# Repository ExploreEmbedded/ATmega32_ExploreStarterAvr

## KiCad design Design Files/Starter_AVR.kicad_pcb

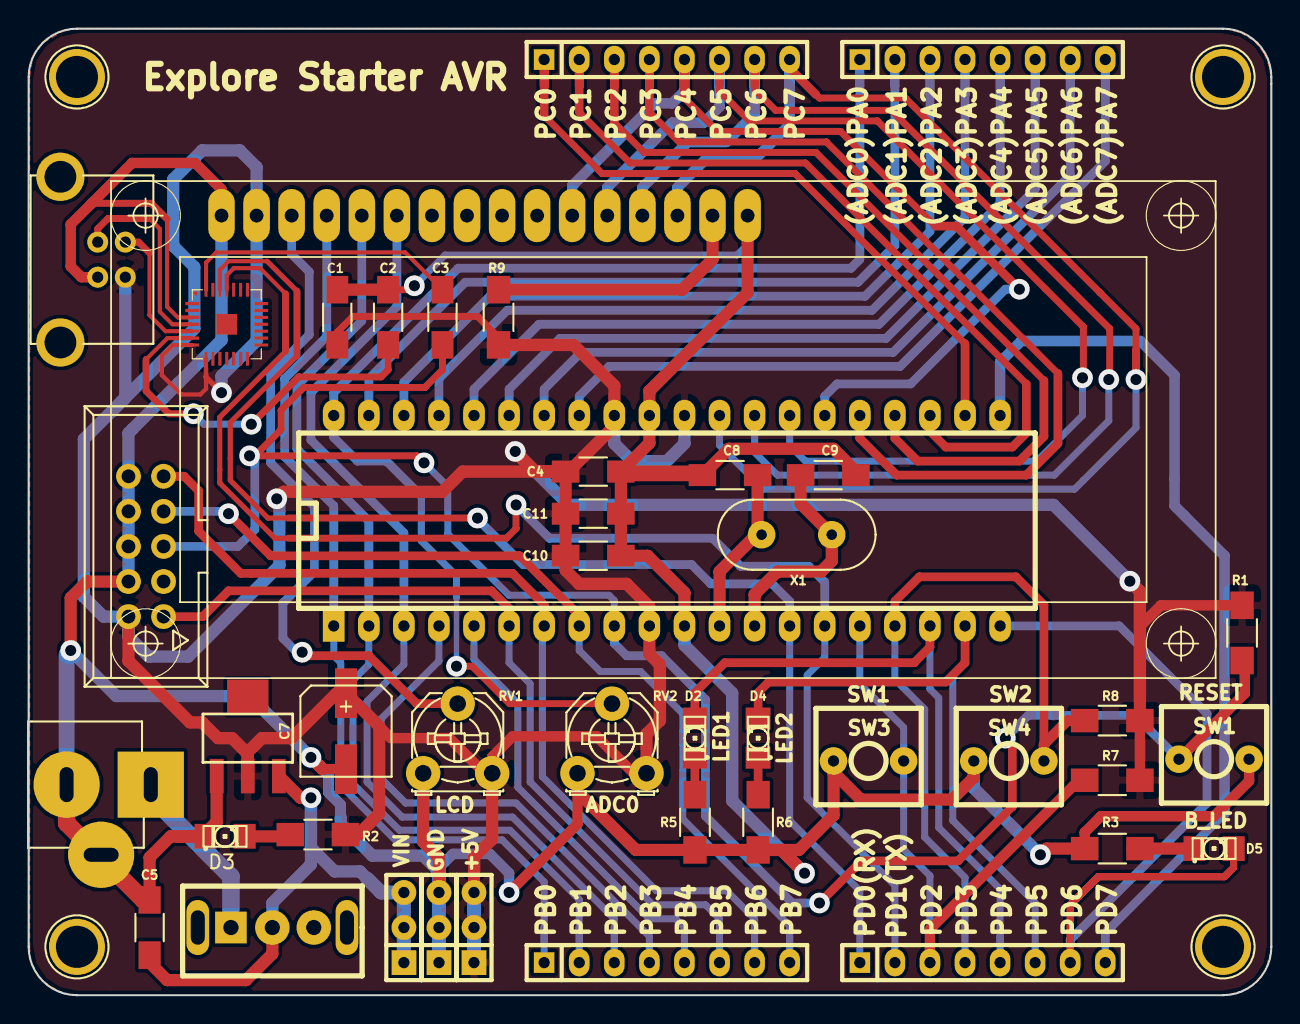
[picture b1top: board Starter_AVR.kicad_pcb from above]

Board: 2 copper layers, 90.0 x 70.0 mm, 47 parts (0 on the bottom side), 49 nets.

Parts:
C1, C2, C3, C4, C5, C10, C11: 0.1uF; C_1206_HandSoldering
C7: 100uF, 25V; c_elec_6.3x4.5
C8, C9: 22pF; C_1206_HandSoldering
CON1: USB-MICRO-B; USB_B
D2, D3, D4, D5: LED; LED-1206_NEW
IC1: ATMEGA32-P; DIP-40__600_ELL
J2, J3, J4, J5: SIL8; SIL-8_xl
K1: BARREL; DC_Jack
K2, K3, K4: CONN_3; SIL-3
LCD1: LCD_2X16_SIL; lcd_2x16_led_backlight-HY-1602F
P1, P2, P3, P4: CONN_1; 1pin
P6: CONN_5X2; VASCH5x2
R1: 10K; R_1206_HandSoldering
R2: 470; R_1206_HandSoldering
R3, R5, R6: 470r; R_1206_HandSoldering
R7, R8: 10k; R_1206_HandSoldering
R9: 2.2k; R_1206_HandSoldering
RV1, RV2: 10K; Potentiometer_Triwood_RM-065
SW1: rst; SW_PUSH_SMALL_2pin_3D_xl
SW2: SPST; SlideSwitch_Big
SW3, SW4: SPST; SW_PUSH_SMALL_2pin_3D_xl
U1: CP2102; cp2102_xl2
U2: LM317S; lm1117_xl
X1: 16Mhz; HC-49V

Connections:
/+5V: C1.1, C4.1, C7.1, C10.1, C11.1, CON1.1, IC1.10, IC1.30, IC1.32, K2.1, K2.2, K2.3, LCD1.2, P6.2, R1.2, R2.2, R7.2, R8.2, R9.1, RV1.3, RV2.3, U1.7, U1.8, U2.2
/ADC0: IC1.40, J2.1, RV2.2
/BL: D5.1, IC1.20, J5.7
/D4: IC1.26, J4.5, LCD1.11
/D5: IC1.27, J4.6, LCD1.12
/D6: IC1.28, J4.7, LCD1.13
/D7: IC1.29, J4.8, LCD1.14
/DC IN: C5.1, K4.1, K4.2, K4.3, SW2.2, U2.3
/DRST: C3.1, U1.28
/E: IC1.3, J3.3, LCD1.6
/L1: D2.1, IC1.18, J5.5
/L2: D4.1, IC1.19, J5.6
/MISO: IC1.7, J3.7, P6.9
/MOSI: IC1.6, J3.6, P6.1
/R/W: IC1.2, J3.2, LCD1.5
/RS: IC1.1, J3.1, LCD1.4
/S1: IC1.16, J5.3, R7.1, SW3.2
/S2: IC1.17, J5.4, R8.1, SW4.2
/SCK: IC1.8, J3.8, P6.7
/rst: C3.2, IC1.9, P6.5, R1.1, SW1.1
/rxd: IC1.14, J5.1, U1.26
/txd: IC1.15, J5.2, U1.25
GND: C1.2, C2.1, C4.2, C5.2, C7.2, C8.1, C9.1, C10.2, C11.2, CON1.4, D3.2, IC1.11, IC1.31, K1.2, K1.3, K3.1, K3.2, K3.3, LCD1.1, LCD1.16, P6.4, P6.6, P6.8, P6.10, R3.1, R5.1, R6.1, RV1.1, RV2.1, SW1.2, SW3.1, SW4.1, U1.3, U2.1
unnamed: C2.2, U1.6
unnamed: C8.2, IC1.12, X1.2
unnamed: C9.2, IC1.13, X1.1
unnamed: CON1.2, U1.5
unnamed: CON1.3, U1.4
unnamed: D2.2, R5.2
unnamed: D3.1, R2.1
unnamed: D4.2, R6.2
unnamed: D5.2, R3.2
unnamed: IC1.4, J3.4
unnamed: IC1.5, J3.5
unnamed: IC1.21, J5.8
unnamed: IC1.22, J4.1
unnamed: IC1.23, J4.2
unnamed: IC1.24, J4.3
unnamed: IC1.25, J4.4
unnamed: IC1.33, J2.8
unnamed: IC1.34, J2.7
unnamed: IC1.35, J2.6
unnamed: IC1.36, J2.5
unnamed: IC1.37, J2.4
unnamed: IC1.38, J2.3
unnamed: IC1.39, J2.2
unnamed: K1.1, SW2.1
unnamed: LCD1.3, RV1.2
unnamed: LCD1.15, R9.2

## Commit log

2016-03-23 added design files
2016-03-23 Added files folder
2016-04-19 Starter_AVR_Complete
    Tutorials and code updated.
2016-12-08 Code and BOM updated
2017-03-29 fixed ADC issue
    fixed ADC issue for atmega32
2017-03-29 Added Boot Loader file
    Added Boot Loader file
